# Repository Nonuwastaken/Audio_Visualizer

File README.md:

# Audio Visualizer

Compact ESP32-C3 audio visualizer — captures sound via an I2S microphone, displays live levels on an OLED, and drives an RGB LED strip through MOSFET channels for real-time audio-reactive lighting. 

## Overview

The system listens to ambient/line audio through an I2S MEMS microphone, computes amplitude in real time on the ESP32-C3, and maps it to:

- An OLED readout of live audio levels
- RGB LED strip brightness/color, switched via high-power MOSFET modules (one channel per color)

## Hardware

Built around an ESP32-C3, an INMP441 I2S microphone, a 0.96" I2C OLED, and an RGB LED strip driven through XY-MOS MOSFET modules. Full component list and costs are linked below.

### Pin Assignments

- **XY-MOS (R/G/B channels):** GPIO 0 / 1 / 3
- **INMP441 (I2S mic):** SCK = GPIO 4, WS = GPIO 5, SD = GPIO 6
- **SSD1306 OLED (I2C):** SDA = GPIO 21, SCL = GPIO 20

## Tuning Sensitivity

You can adjust how the visualizer reacts by editing these parameters at the top of each sketch:

```cpp
// 1. VOLUME THRESHOLDS
#define NOISE_FLOOR     5000
#define MAX_LOUDNESS    13500

// 2. FADING SPEEDS (0.01 to 1.0)
#define FADE_UP_SPEED   1.0   // Higher = snappier reaction to loud beats
#define FADE_DOWN_SPEED 0.1   // Lower = slower, smoother fade out between beats
```

| Parameter | What it does | Tune it if... |
|---|---|---|
| `NOISE_FLOOR` | Amplitude below this is treated as silence (LEDs off) | LEDs flicker in a quiet room → raise it. Lights don't react to soft sounds → lower it |
| `MAX_LOUDNESS` | Amplitude at which the LEDs hit full brightness | LEDs are always maxed out → raise it. Never get bright enough → lower it |
| `FADE_UP_SPEED` | How fast brightness rises with sound (0.01–1.0) | Want a snappier reaction to beats → raise it |
| `FADE_DOWN_SPEED` | How fast brightness falls after a sound (0.01–1.0) | Want a smoother, slower fade-out → lower it |

The ideal values depend on your microphone, its placement, and the room, so tune them to your setup. A good approach is to start with `NOISE_FLOOR` just above your quiet-room baseline, then adjust `MAX_LOUDNESS` until the lights peak on your loudest sounds.

## Code Variants

Several sketches are included, each driving the RGB strip differently while sharing the same I2S/OLED core:

| Sketch | Behavior |
|---|---|
| `multi_colour_audio.ino` | Audio-reactive brightness with a slow, continuously shifting hue cycle across R/G/B |
| `red_audio.ino` | Audio-reactive brightness, fixed red |
| `green_audio.ino` | Audio-reactive brightness, fixed green |
| `blue_audio.ino` | Audio-reactive brightness, fixed blue |
| `cyan_audio.ino` | Audio-reactive brightness, fixed cyan |
| `purple_audio.ino` | Audio-reactive brightness, fixed purple |
| `yellow_audio.ino` | Audio-reactive brightness, fixed yellow |
| `white_audio.ino` | Audio-reactive brightness, fixed white (all channels) |

## Circuit Diagram

https://app.cirkitdesigner.com/project/735b4f31-fd71-42aa-8f38-7ad56208304c

## PCB & Enclosure

- **PCB:** The custom V2 PCB design files are available in the `Custom_PCB` folder.
- **Enclosure (CAD):** A custom enclosure was designed for the V2 board. The source CAD files are available in the `CAD Model` folder.

**Onshape CAD:**  
https://cad.onshape.com/documents/6593946ba04cc1c559037129/w/a2d187fac915f00b7de97ec5/e/4e3bb7f6afe98f245e745010?renderMode=0&uiState=6ac3de645add55faa27b7aaf

> **Note:** If you encounter a 403 Forbidden error, copy the link and open it in a new tab.

> [!IMPORTANT]
> **Manual wiring required!** The PCB does not connect everything for you:
>
> 1. **Wire GND and VIN- of the MOSFET modules** by hand with a wire.
> 2. **Screw the LED strip wires** into the screw terminals on the MOSFET modules/PCB according to the circuit diagram given.
>
> Skip these and the LED strip won't light up.

### PCB Mounting Holes

The PCB mounting holes in the CAD model are sized for **M3 heat-set inserts**. If you're using something different, adjust the hole size in the CAD model:

- **Other bolt/insert sizes:** change the hole diameter to match your hardware.
- **Screwing directly into the plastic (no inserts):** set the hole diameter to **2.9-3 mm** (For M3).

## Component List

- V1: https://docs.google.com/spreadsheets/d/1ALqold5_36gFdbRfQ2sbJwHor0Tc50hgfMq46gXfjWg/edit?usp=sharing
- V2: https://docs.google.com/spreadsheets/d/10Zfk7NXO29kVGQfq_vPPTgnpW9qup-5_QyMn6JiCvyc/edit?usp=sharing

## Status

- **V1:** complete and functional, built on perfboard with screw-terminal connections.
- **V2:** complete. The perfboard/screw-terminal wiring has been replaced with a custom PCB, and a custom enclosure has been designed to house it, making the project easier to replicate and more robust.

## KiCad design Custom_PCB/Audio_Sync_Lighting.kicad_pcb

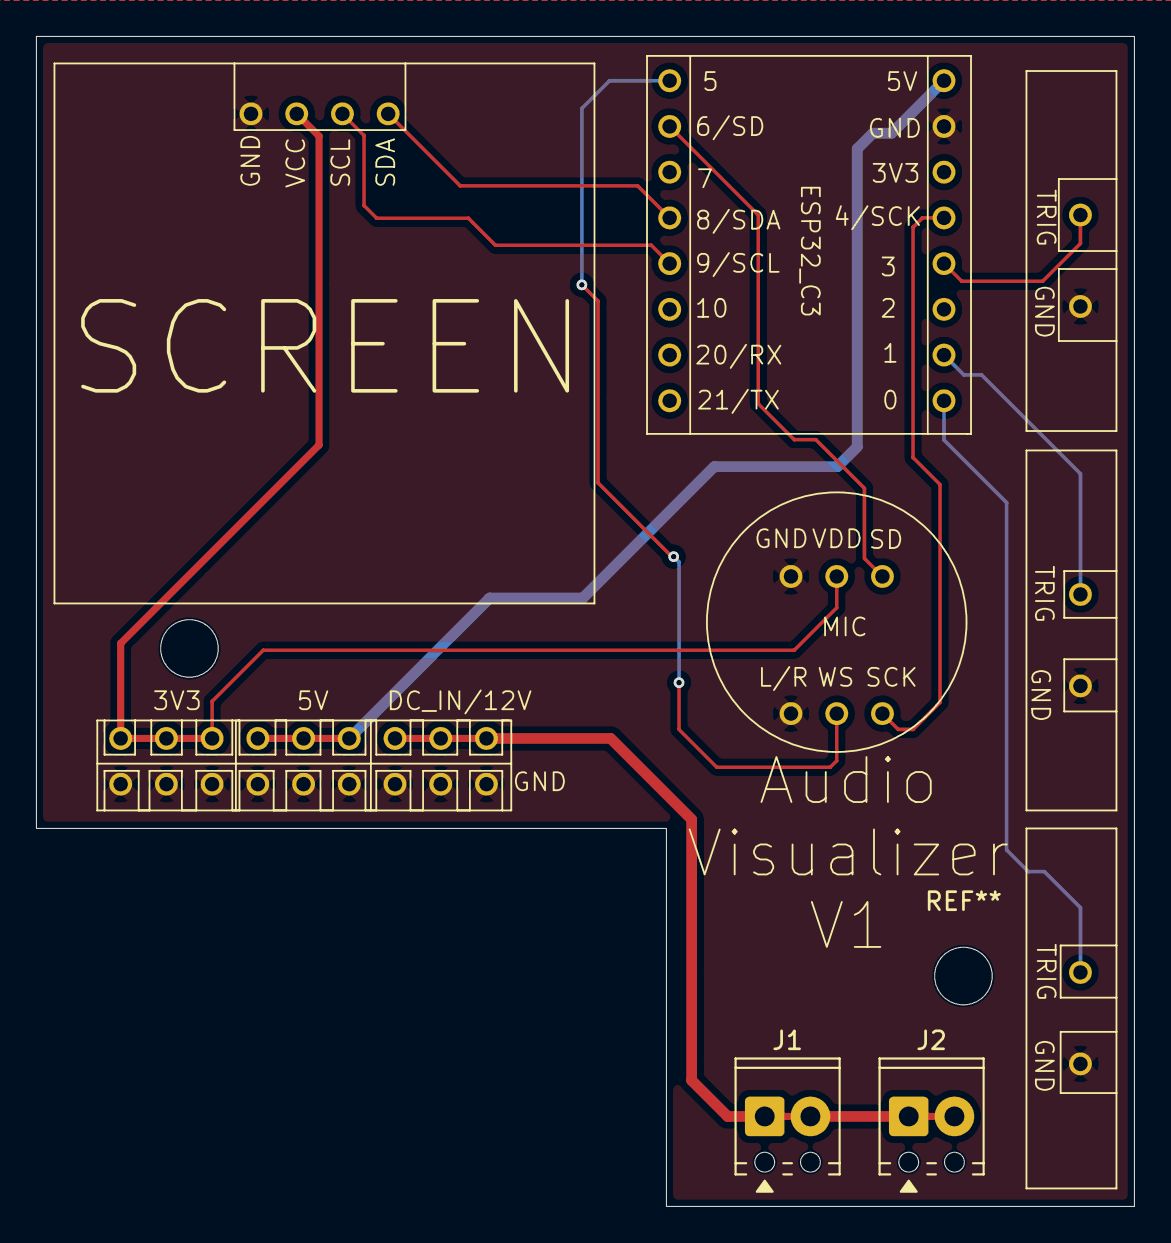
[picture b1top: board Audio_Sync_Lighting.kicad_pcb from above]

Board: 2 copper layers, 61.0 x 65.0 mm, 9 parts (0 on the bottom side), 12 nets.

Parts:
J1, J2: Screw_Terminal_01x02; TerminalBlock_Phoenix_MPT-0,5-2-2.54_1x02_P2.54mm_Horizontal
U1: ESP32_C3; ESP32_C3_SuperMini
U2: 0.96_OLED
U3: Microphone; INMP441_Microphone
U4, U5, U8: XY_MOS
U7: Buck; Buck_Multi_Output

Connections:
+3.3V: U2.2 (3V3), U3.5 (VDD), U7.3 (3V3)
+5V: U1.9 (5V), U7.1 (5V)
GND: U1.10 (GND), U2.1 (GND), U3.1 (L/R), U3.4 (GND), U4.1 (GND), U5.1 (GND), U7.2 (GND), U8.1 (GND)
unnamed: J1.1, J1.2, J2.1, J2.2, U7.4 (DC_IN)
unnamed: U1.16 (0), U8.2 (TRIG)
unnamed: U1.15 (1), U5.2 (TRIG)
unnamed: U1.13 (3), U4.2 (TRIG)
unnamed: U1.12 (4/SCK), U3.3 (SCK)
unnamed: U1.1 (5), U3.2 (WS)
unnamed: U1.2 (6/SD), U3.6 (SD)
unnamed: U1.4 (8/SDA), U2.4 (SDA)
unnamed: U1.5 (9/SCL), U2.3 (SCK)
